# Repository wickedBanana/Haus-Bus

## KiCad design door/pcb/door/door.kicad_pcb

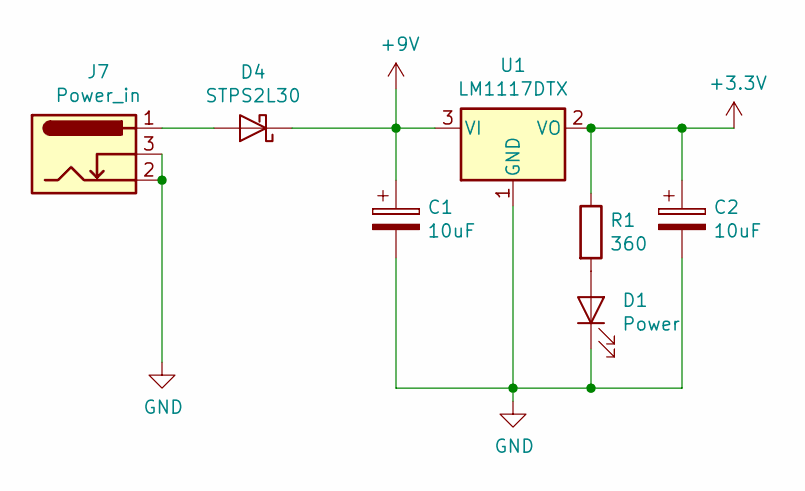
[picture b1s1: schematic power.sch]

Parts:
C1, C2: 10uF; CP_EIA-3216-10_Kemet-I
D1: Power; LED_1206_3216Metric
D4: STPS2L30; D_SMA
J7: Power_in; BarrelJack_Wuerth_6941xx301002
R1: 360; R_0805_2012Metric
U1: LM1117DTX; SOT-223

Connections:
+3V3: C2.1, R1.1, U1.2 (VO); also elsewhere on the board
+9V: C1.1, D4.1 (K), U1.3 (VI); also elsewhere on the board
unnamed: D1.2 (A), R1.2
unnamed: D4.2 (A), J7.1

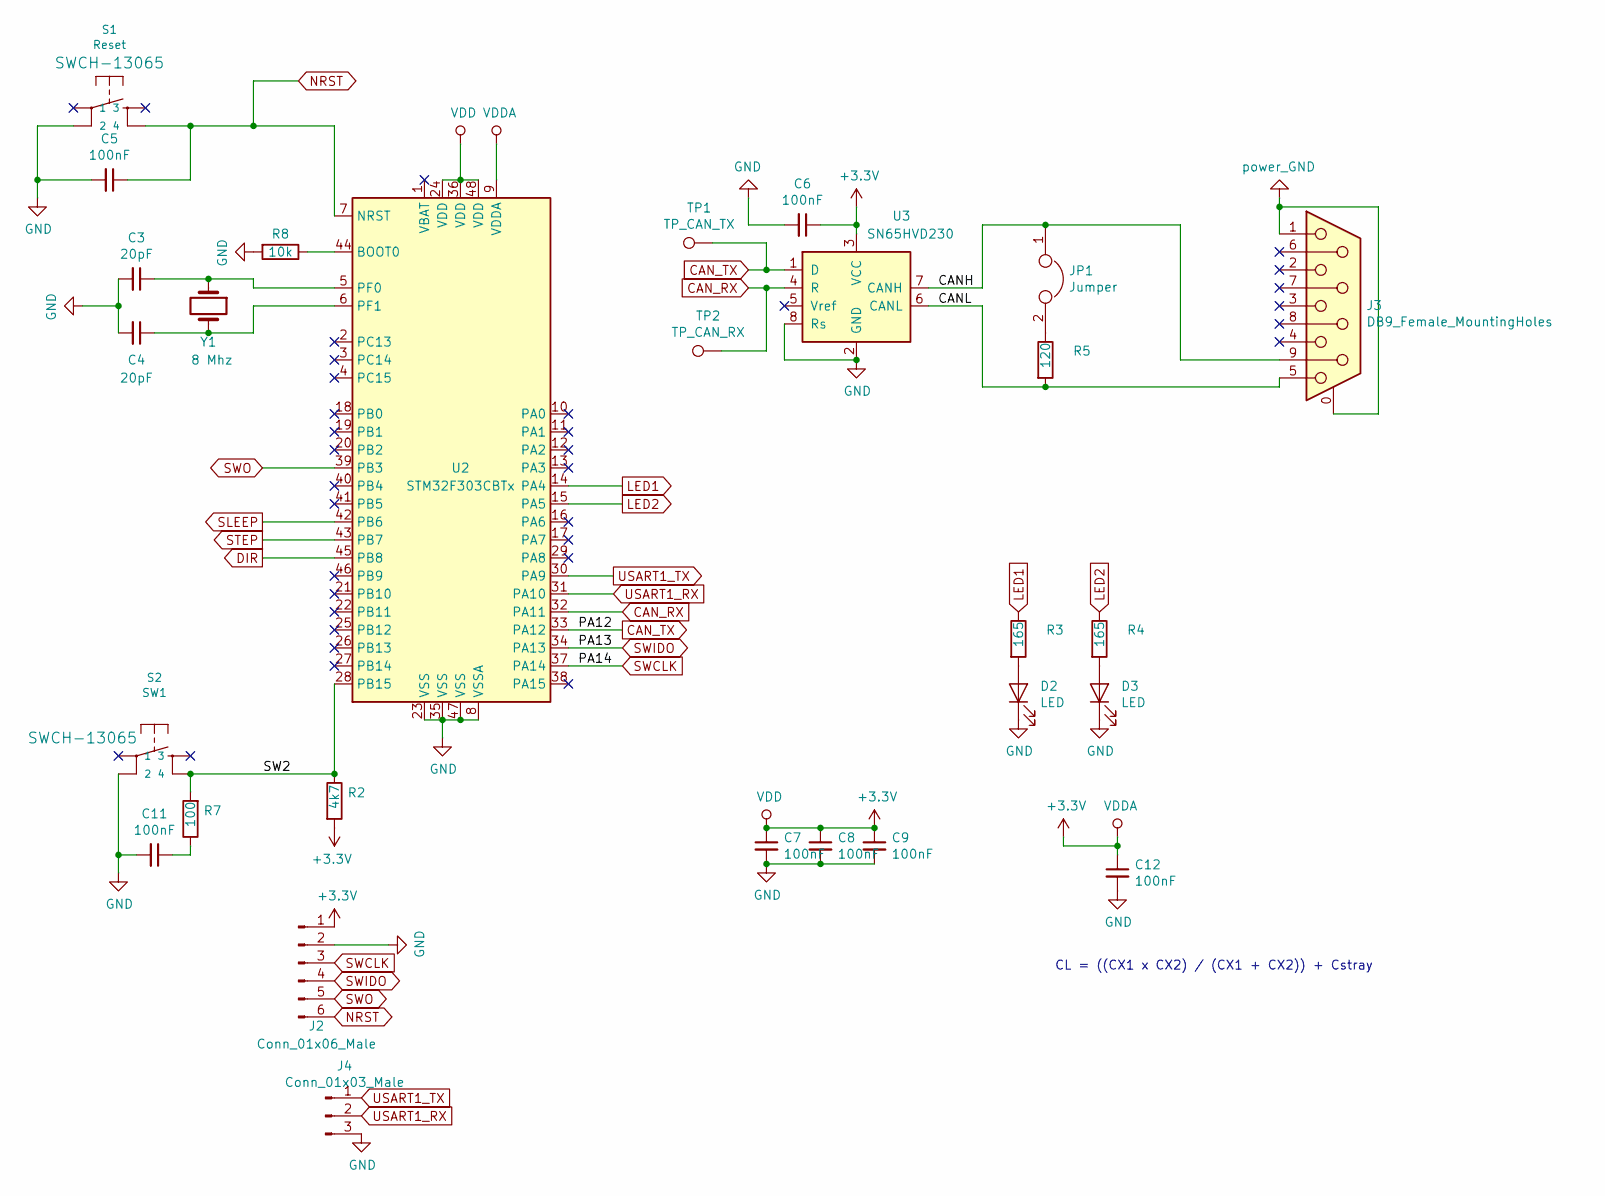
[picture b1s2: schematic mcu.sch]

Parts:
C3, C4: 20pF; C_0805_2012Metric
C5, C6, C7, C8, C9, C11, C12: 100nF; C_0805_2012Metric
D2, D3: LED; LED_1206_3216Metric
J2: Conn_01x06_Male; PinHeader_1x06_P2.54mm_Vertical
J3: DB9_Female_MountingHoles; DSUB-9_Female_Horizontal_P2.77x2.84mm_EdgePinOffset4.94mm_H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
J4: Conn_01x03_Male; PinHeader_1x03_P2.54mm_Vertical
JP1: Jumper; PinHeader_1x02_P2.54mm_Vertical
R2: 4k7; R_0805_2012Metric
R3, R4: 165; R_0805_2012Metric
R5: 120; R_0805_2012Metric
R7: 100; R_0805_2012Metric
R8: 10k; R_0805_2012Metric
S1: Reset; TACTILE_SWITCH_SMD_4.6X2.8MM
S2: SW1; TACTILE_SWITCH_SMD_4.6X2.8MM
TP1: TP_CAN_TX; TestPoint_Pad_D1.0mm
TP2: TP_CAN_RX; TestPoint_Pad_D1.0mm
U2: STM32F303CBTx; LQFP-48_7x7mm_P0.5mm
U3: SN65HVD230; SOIC-8_3.9x4.9mm_P1.27mm
Y1: 8 Mhz; Crystal_HC49-U_Vertical

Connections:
+3V3: C6.1, C7.1, C8.1, C9.1, C12.1, J2.1, R2.2, U2.9 (VDDA), U2.24 (VDD), U2.36 (VDD), U2.48 (VDD), U3.3 (VCC); also elsewhere on the board
/mcu/CANH: J3.9, JP1.1, U3.7 (CANH)
/mcu/CANL: J3.5, R5.2, U3.6 (CANL)
/mcu/SW2: R2.1, R7.2, S2.4, U2.28 (PB15)
CAN_RX: TP2.1, U2.32 (PA11), U3.4 (R)
CAN_TX: TP1.1, U2.33 (PA12), U3.1 (D)
DIR: U2.45 (PB8); also elsewhere on the board
LED1: R3.1, U2.14 (PA4)
LED2: R4.1, U2.15 (PA5)
NRST: C5.1, J2.6, S1.4, U2.7 (NRST)
unnamed: C3.1, U2.5 (PF0), Y1.1
unnamed: C4.1, U2.6 (PF1), Y1.2
unnamed: C11.1, R7.1
unnamed: D2.2 (A), R3.2
unnamed: D3.2 (A), R4.2
unnamed: JP1.2, R5.1
unnamed: R8.1, U2.44 (BOOT0)
SLEEP: U2.42 (PB6); also elsewhere on the board
STEP: U2.43 (PB7); also elsewhere on the board
SWCLK: J2.3, U2.37 (PA14)
SWIDO: J2.4, U2.34 (PA13)
SWO: J2.5, U2.39 (PB3)
USART1_RX: J4.2, U2.31 (PA10)
USART1_TX: J4.1, U2.30 (PA9)

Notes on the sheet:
CL = ((CX1 x CX2) / (CX1 + CX2)) + Cstray

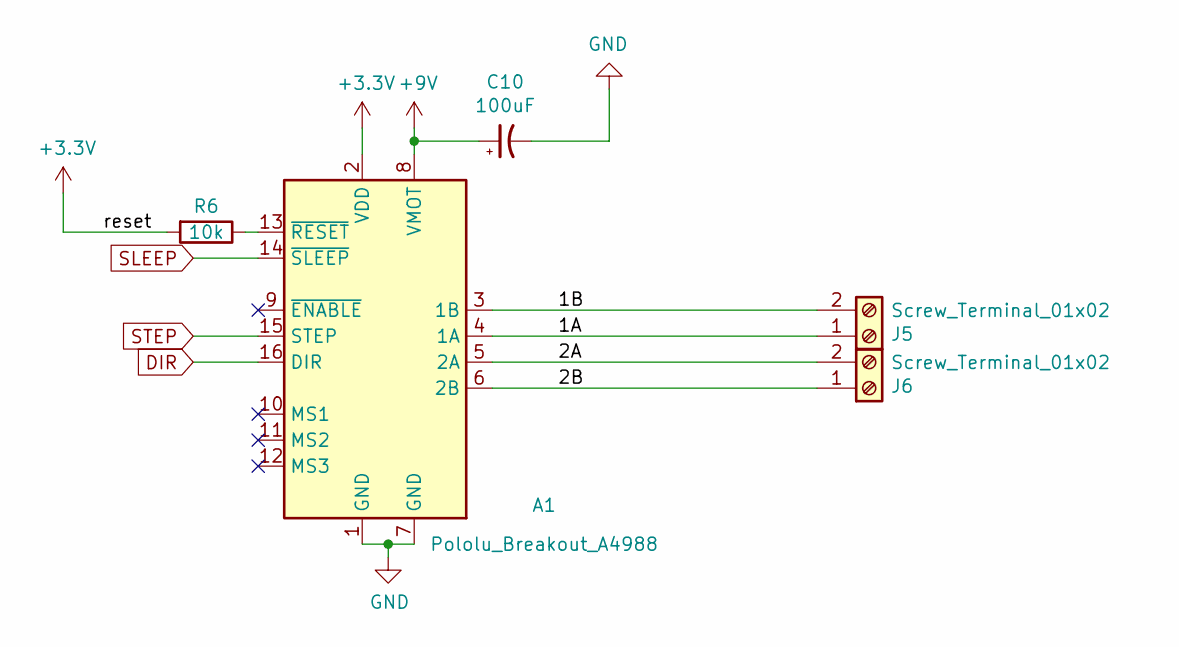
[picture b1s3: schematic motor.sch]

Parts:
A1: Pololu_Breakout_A4988; Pololu_Breakout-16_15.2x20.3mm
C10: 100uF; CP_Elec_6.3x5.4
J5, J6: Screw_Terminal_01x02; TerminalBlock_Phoenix_MKDS-1,5-2-5.08_1x02_P5.08mm_Horizont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
R6: 10k; R_0805_2012Metric

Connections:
+3V3: A1.2 (VDD), R6.2; also elsewhere on the board
+9V: A1.8 (VMOT), C10.1; also elsewhere on the board
/motor/1A: A1.4 (1A), J5.1
/motor/1B: A1.3 (1B), J5.2
/motor/2A: A1.5 (2A), J6.2
/motor/2B: A1.6 (2B), J6.1
DIR: A1.16 (DIR); also elsewhere on the board
unnamed: A1.13 (~RESET), R6.1
SLEEP: A1.14 (~SLEEP); also elsewhere on the board
STEP: A1.15 (STEP); also elsewhere on the board

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
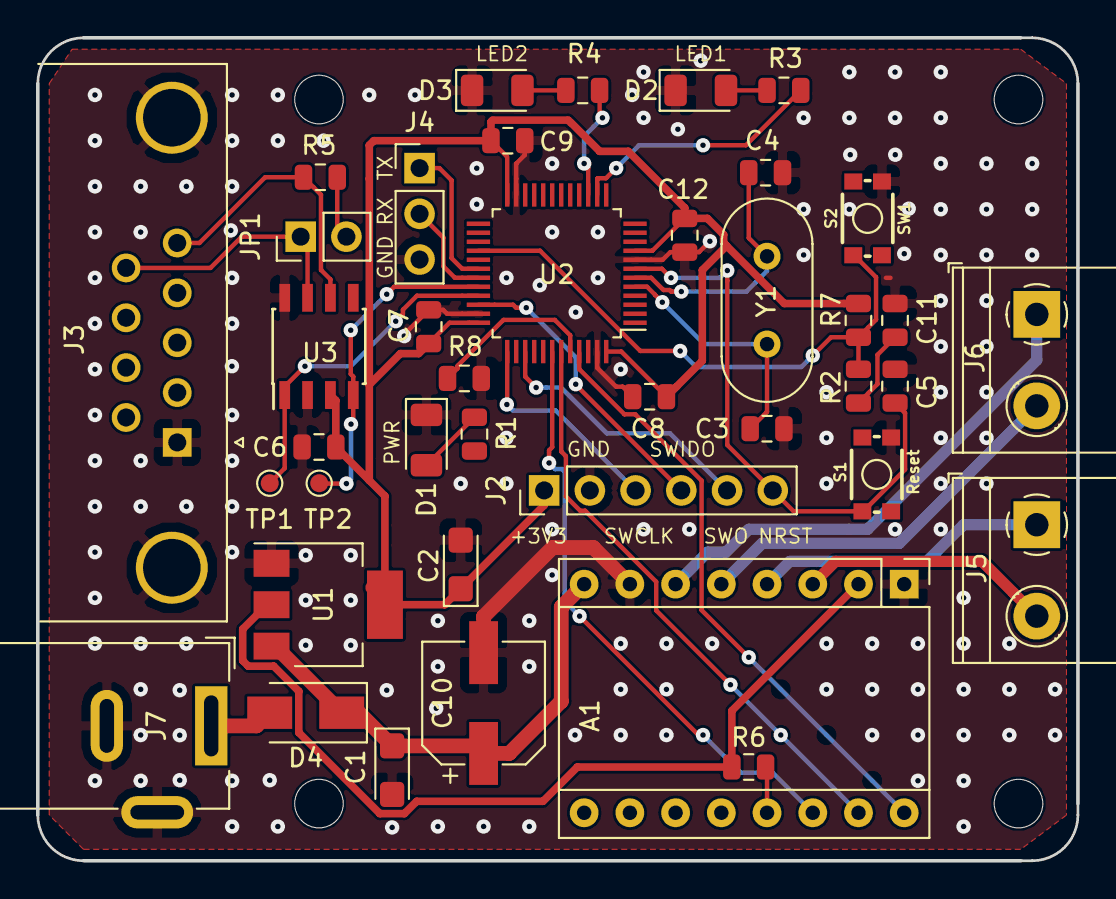
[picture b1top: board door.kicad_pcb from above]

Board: 2 copper layers, 57.8 x 45.7 mm, 40 parts (0 on the bottom side), 33 nets.

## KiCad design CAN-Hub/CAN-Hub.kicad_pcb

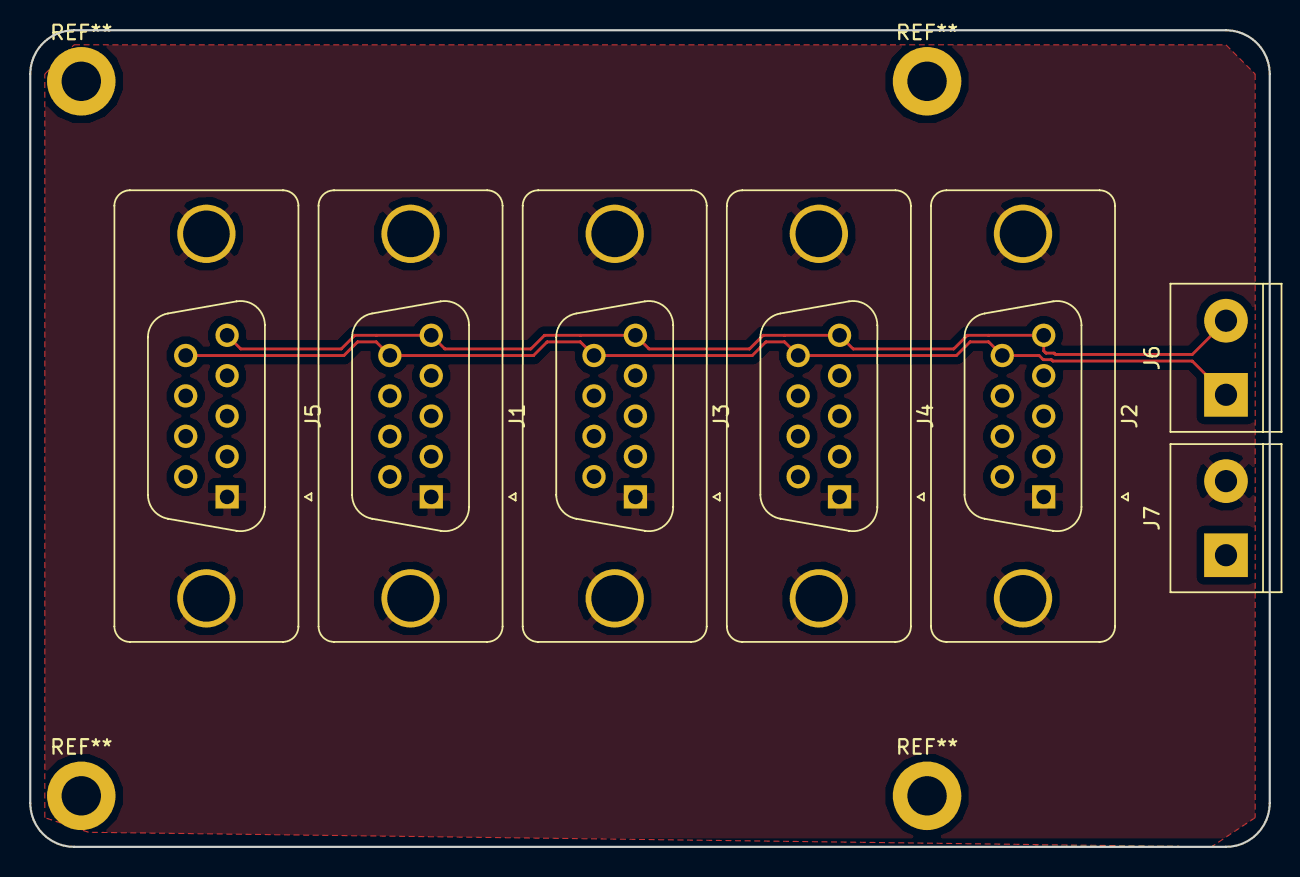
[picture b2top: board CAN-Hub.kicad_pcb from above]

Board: 2 copper layers, 85.0 x 56.0 mm, 7 parts (0 on the bottom side), 3 nets.

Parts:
J1, J2, J3, J4, J5: DB9_Male_MountingHoles; DSUB-9_Female_Vertical_P2.77x2.84mm_MountingHoles
J6, J7: Connector_Screw_Terminal_01x02; TerminalBlock_bornier-2_P5.08mm

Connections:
/can+: J1.9, J2.9, J3.9, J4.9, J5.9, J6.1
/can-: J1.5, J2.5, J3.5, J4.5, J5.5, J6.2
GND: J1.0, J1.1, J2.0, J2.1, J3.0, J3.1, J4.0, J4.1, J5.0, J5.1, J7.2

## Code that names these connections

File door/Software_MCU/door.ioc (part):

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Mcu.Name=STM32F303C(B-C)Tx
Mcu.Package=LQFP48
Mcu.UserName=STM32F303CBTx
PA10.Mode=Asynchronous
PA10.Signal=USART1_RX
PA11.Mode=Master
PA11.Signal=CAN_RX
PA12.Mode=Master
PA12.Signal=CAN_TX
PA13.Mode=Serial_Wire
PA13.Signal=SYS_JTMS-SWDIO
PA14.Mode=Serial_Wire
PA14.Signal=SYS_JTCK-SWCLK
PA4.Signal=COMP_DAC1_group
PA5.GPIOParameters=GPIO_Label
PA5.GPIO_Label=LED2
PA5.Signal=GPIO_Output
PA9.Mode=Asynchronous
PA9.Signal=USART1_TX
PB15.GPIOParameters=GPIO_Label
PB15.GPIO_Label=SW1
PB15.Signal=GPIO_Input
PB6.GPIOParameters=GPIO_Label
PB6.GPIO_Label=STEP
PB6.Signal=GPIO_Input
PB7.GPIOParameters=GPIO_Label
PB7.GPIO_Label=SLEEP
PB7.Signal=GPIO_Output
PB8.GPIOParameters=GPIO_Label
PB8.GPIO_Label=DIR
PB8.Signal=GPIO_Output
PF0-OSC_IN.Mode=HSE-External-Oscillator
PF0-OSC_IN.Signal=RCC_OSC_IN
PF1-OSC_OUT.Mode=HSE-External-Oscillator
PF1-OSC_OUT.Signal=RCC_OSC_OUT
RCC.HSEPLLFreq_Value=8000000
RCC.HSE_VALUE=8000000
RCC.SYSCLKFreq_VALUE=72000000
RCC.SYSCLKSourceVirtual=RCC_SYSCLKSOURCE_PLLCLK
board=custom

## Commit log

2018-11-17 usb stecker getauscht
2018-11-17 caps voltage regulator gestauscht
2018-11-17 Taster
2018-11-17 stm32 projekt geaddet
2018-11-18 readme geaddet
2018-11-18 beschriftung
2018-11-25 100uF für Motortreiber geaddet
2018-11-26 layout überarbeitet
2018-11-26 layout 100uF elko überarbeitet
2018-11-28 track width adjusted
2018-11-29 recplaced usb micro jack with barrel-jack, reworked pcb layout
2018-11-29 labeling and trackwidth
2018-11-30 adjusted value of power led to 9V
2018-12-01 updated pcb ground plane layout
2018-12-03 reverse voltage protection added
2018-12-12 readme
2018-12-12 readme.md
2018-12-21 added some 3d-models
2018-12-21 added 3d-models for the push buttons
2018-12-21 updated image
2018-12-23 added silkscreen labels for the usart pin header
2019-02-09 changed pinout of DB-9 connector
2019-02-09 added CAN-Hub
2019-02-09 added readme
2019-02-09 verical connectors
2019-03-24 corrected error in Layout swido was connected with Can Rx
2019-03-24 added polarity protection diode
